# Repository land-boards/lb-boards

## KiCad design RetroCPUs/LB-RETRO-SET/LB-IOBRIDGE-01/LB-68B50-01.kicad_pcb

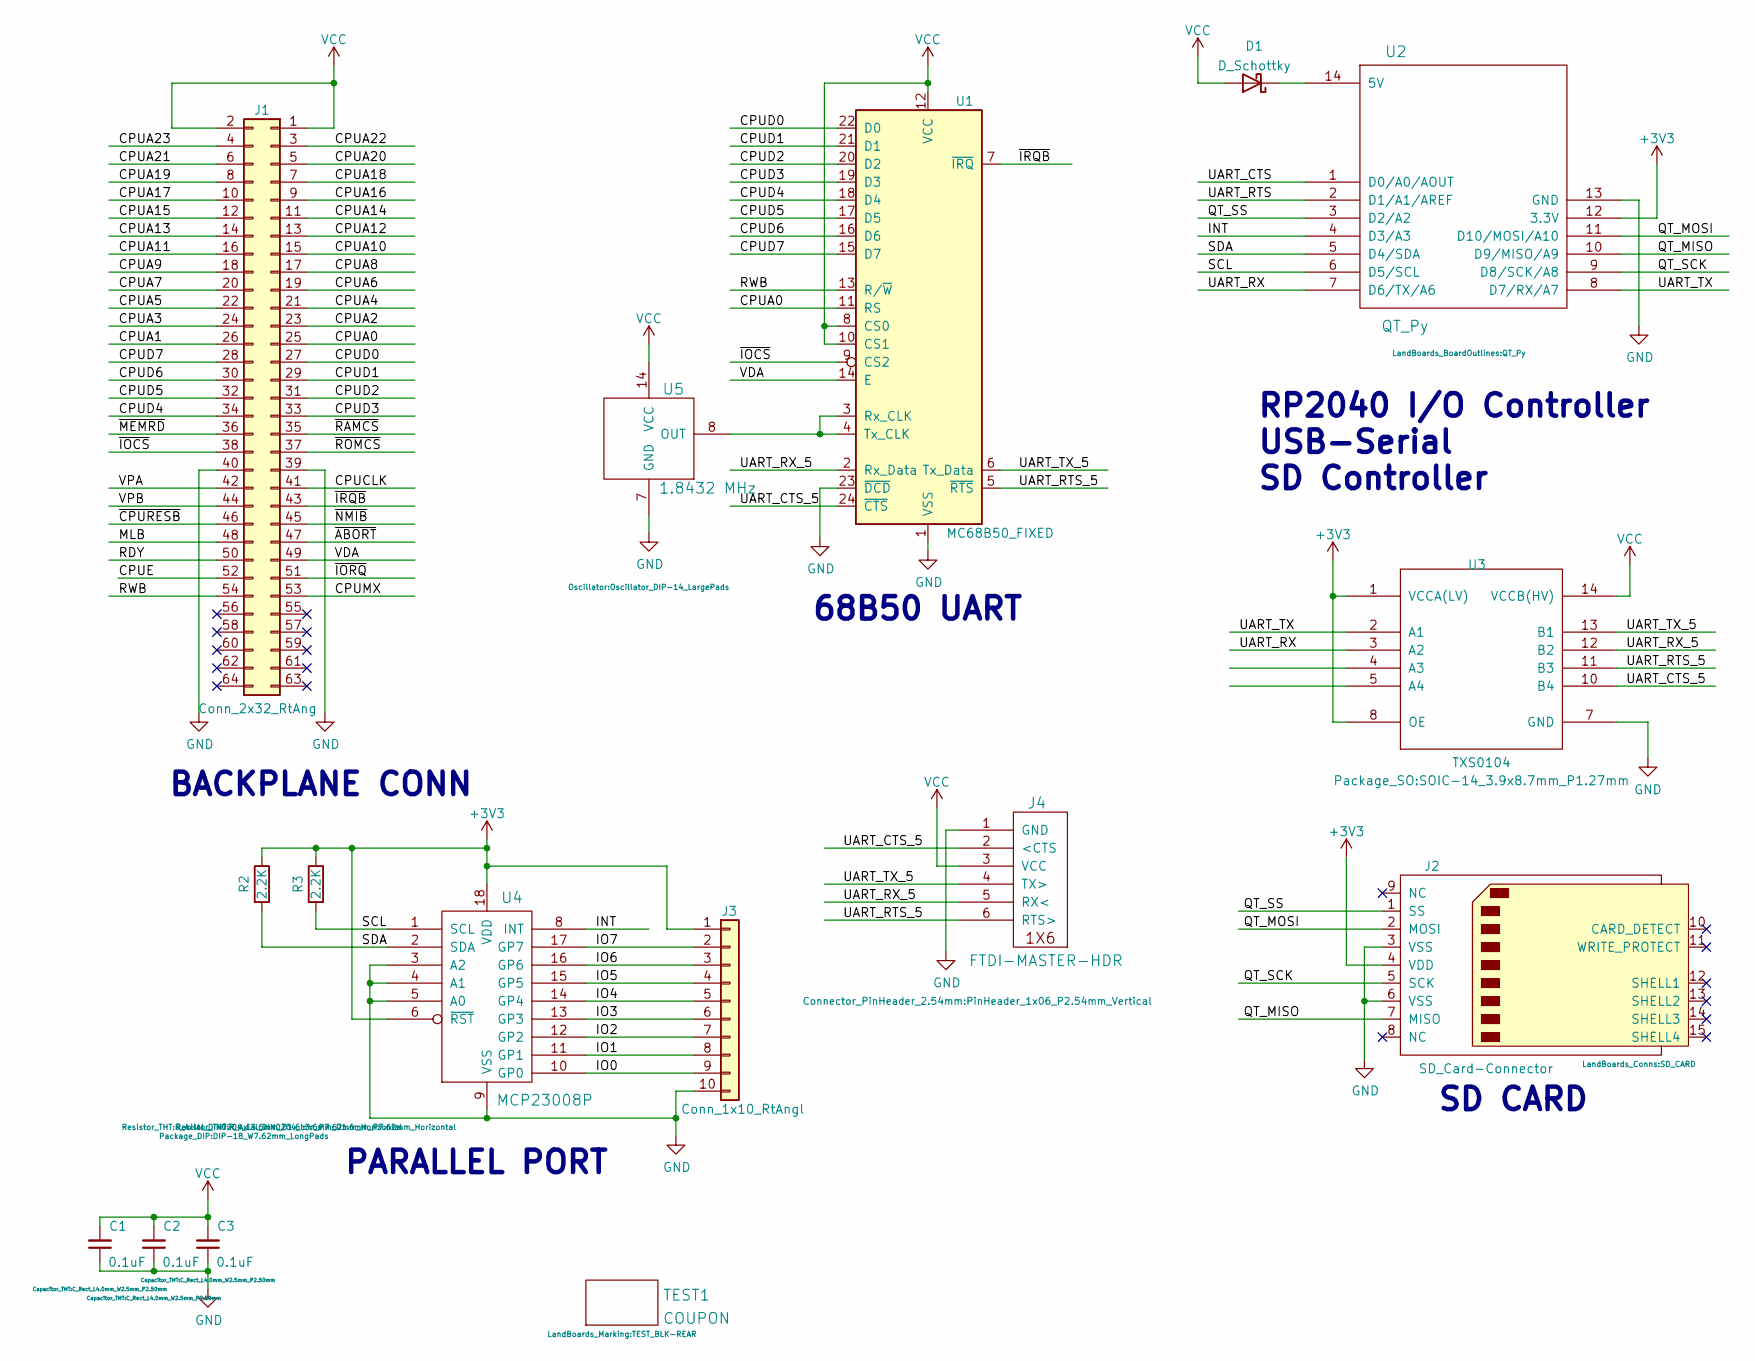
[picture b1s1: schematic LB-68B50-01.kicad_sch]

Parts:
C1, C2, C3: 0.1uF; C_Rect_L4.0mm_W2.5mm_P2.50mm
D1: D_Schottky; D_DO-35_SOD27_P10.16mm_Horizontal
J1: Conn_2x32_RtAng; PinHeader_2x32_P2.54mm_Horizontal-FLIPPED
J2: SD_Card-Connector; SD_CARD
J3: Conn_1x10_RtAngl; PinHeader_1x10_P2.54mm_Horizontal
J4: FTDI-MASTER-HDR; PinHeader_1x06_P2.54mm_Vertical
R2, R3: 2.2K; R_Axial_DIN0204_L3.6mm_D1.6mm_P7.62mm_Horizontal
TEST1: COUPON; TEST_BLK-REAR
U1: MC68B50_FIXED; DIP-24_W15.24mm_LongPads
U2: QT_Py
U3: TXS0104; SOIC-14_3.9x8.7mm_P1.27mm
U4: MCP23008P; DIP-18_W7.62mm_LongPads
U5: 1.8432 MHz; Oscillator_DIP-14_LargePads

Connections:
+3V3: J2.4 (VDD), J3.1, R2.1, R3.1, U2.12 (3.3V), U3.1 (VCCA(LV)), U3.8 (OE), U4.6 (~RST), U4.18 (VDD)
/CPUA0: J1.25, U1.11 (RS)
/CPUA1: J1.26
/CPUA2: J1.23
/CPUA3: J1.24
/CPUA4: J1.21
/CPUA5: J1.22
/CPUA6: J1.19
/CPUA7: J1.20
/CPUA8: J1.17
/CPUA9: J1.18
/CPUA10: J1.15
/CPUA11: J1.16
/CPUA12: J1.13
/CPUA13: J1.14
/CPUA14: J1.11
/CPUA15: J1.12
/CPUA16: J1.9
/CPUA17: J1.10
/CPUA18: J1.7
/CPUA19: J1.8
/CPUA20: J1.5
/CPUA21: J1.6
/CPUA22: J1.3
/CPUA23: J1.4
/CPUCLK: J1.41
/CPUD0: J1.27, U1.22 (D0)
/CPUD1: J1.29, U1.21 (D1)
/CPUD2: J1.31, U1.20 (D2)
/CPUD3: J1.33, U1.19 (D3)
/CPUD4: J1.34, U1.18 (D4)
/CPUD5: J1.32, U1.17 (D5)
/CPUD6: J1.30, U1.16 (D6)
/CPUD7: J1.28, U1.15 (D7)
/CPUE: J1.52
/CPUMX: J1.53
/INT: U2.4 (D3/A3), U4.8 (INT)
/IO0: J3.9, U4.10 (GP0)
/IO1: J3.8, U4.11 (GP1)
/IO2: J3.7, U4.12 (GP2)
/IO3: J3.6, U4.13 (GP3)
/IO4: J3.5, U4.14 (GP4)
/IO5: J3.4, U4.15 (GP5)
/IO6: J3.3, U4.16 (GP6)
/IO7: J3.2, U4.17 (GP7)
/MLB: J1.48
/QT_MISO: J2.7 (MISO), U2.10 (D9/MISO/A9)
/QT_MOSI: J2.2 (MOSI), U2.11 (D10/MOSI/A10)
/QT_SCK: J2.5 (SCK), U2.9 (D8/SCK/A8)
/QT_SS: J2.1 (SS), U2.3 (D2/A2)
/RDY: J1.50
/RWB: J1.54, U1.13 (R/~W)
/SCL: R3.2, U2.6 (D5/SCL), U4.1 (SCL)
/SDA: R2.2, U2.5 (D4/SDA), U4.2 (SDA)
/UART_CTS: U2.1 (D0/A0/AOUT)
/UART_CTS_5: J4.2 (<CTS), U1.24 (~CTS), U3.10 (B4)
/UART_RTS: U2.2 (D1/A1/AREF)
/UART_RTS_5: J4.6 (RTS>), U1.5 (~RTS), U3.11 (B3)
/UART_RX: U2.7 (D6/TX/A6), U3.3 (A2)
/UART_RX_5: J4.5 (RX<), U1.2 (Rx_Data), U3.12 (B2)
/UART_TX: U2.8 (D7/RX/A7), U3.2 (A1)
/UART_TX_5: J4.4 (TX>), U1.6 (Tx_Data), U3.13 (B1)
/VDA: J1.49, U1.14 (E)
/VPA: J1.42
/VPB: J1.44
/~ABORT: J1.47
/~CPURESB: J1.46
/~IOCS: J1.38, U1.9 (CS2)
/~IORQ: J1.51
/~IRQB: J1.43, U1.7 (~IRQ)
/~MEMRD: J1.36
/~NMIB: J1.45
/~RAMCS: J1.35
/~ROMCS: J1.37
GND: C1.1, C2.1, C3.1, J1.39, J1.40, J2.3 (VSS), J2.6 (VSS), J3.10, J4.1 (GND), U1.1 (VSS), U1.23 (~DCD), U2.13 (GND), U3.7 (GND), U4.3 (A2), U4.4 (A1), U4.5 (A0), U4.9 (VSS), U5.7 (GND)
unnamed: D1.1 (K), U2.14 (5V)
unnamed: U1.3 (Rx_CLK), U1.4 (Tx_CLK), U5.8 (OUT)
VCC: C1.2, C2.2, C3.2, D1.2 (A), J1.1, J1.2, J4.3 (VCC), U1.8 (CS0), U1.10 (CS1), U1.12 (VCC), U3.14 (VCCB(HV)), U5.14 (VCC)

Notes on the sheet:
68B50 UART
RP2040 I/O Controller USB-Serial SD Controller
SD CARD
BACKPLANE CONN
PARALLEL PORT

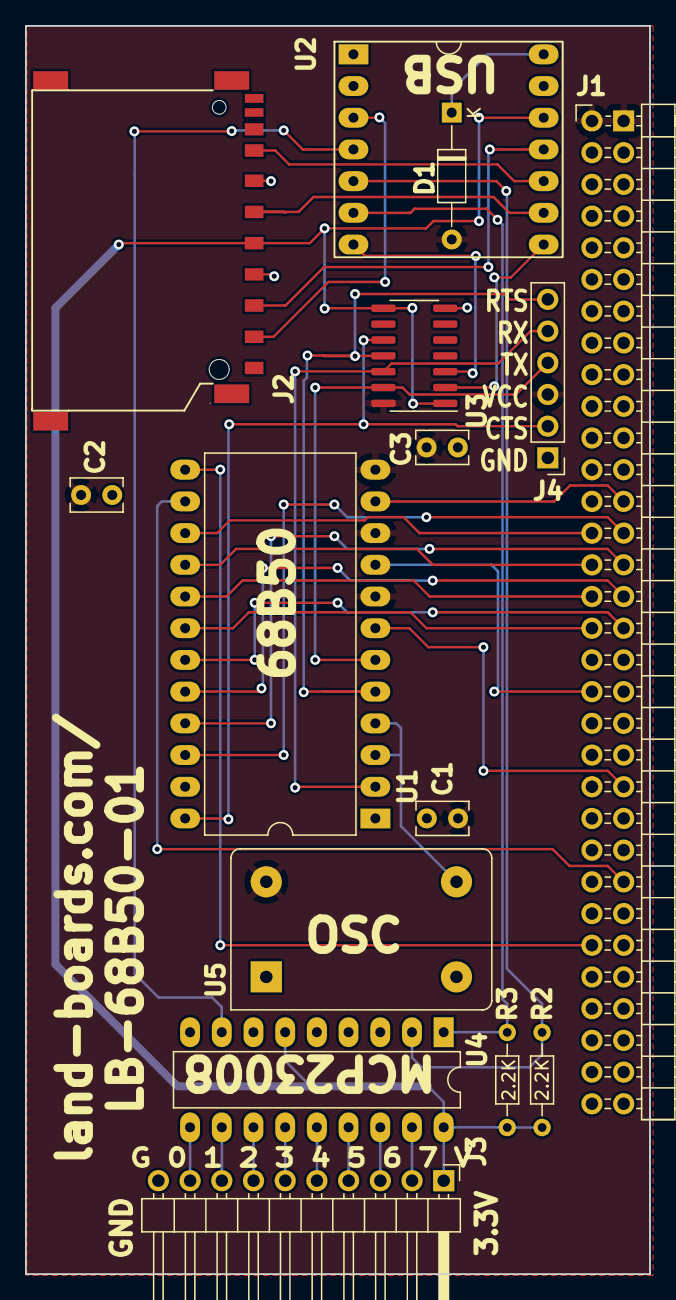
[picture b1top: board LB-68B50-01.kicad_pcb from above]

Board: 2 copper layers, 50.0 x 100.0 mm, 16 parts (0 on the bottom side), 39 nets.

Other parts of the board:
TEST: COUPON; TEST_BLK-REAR

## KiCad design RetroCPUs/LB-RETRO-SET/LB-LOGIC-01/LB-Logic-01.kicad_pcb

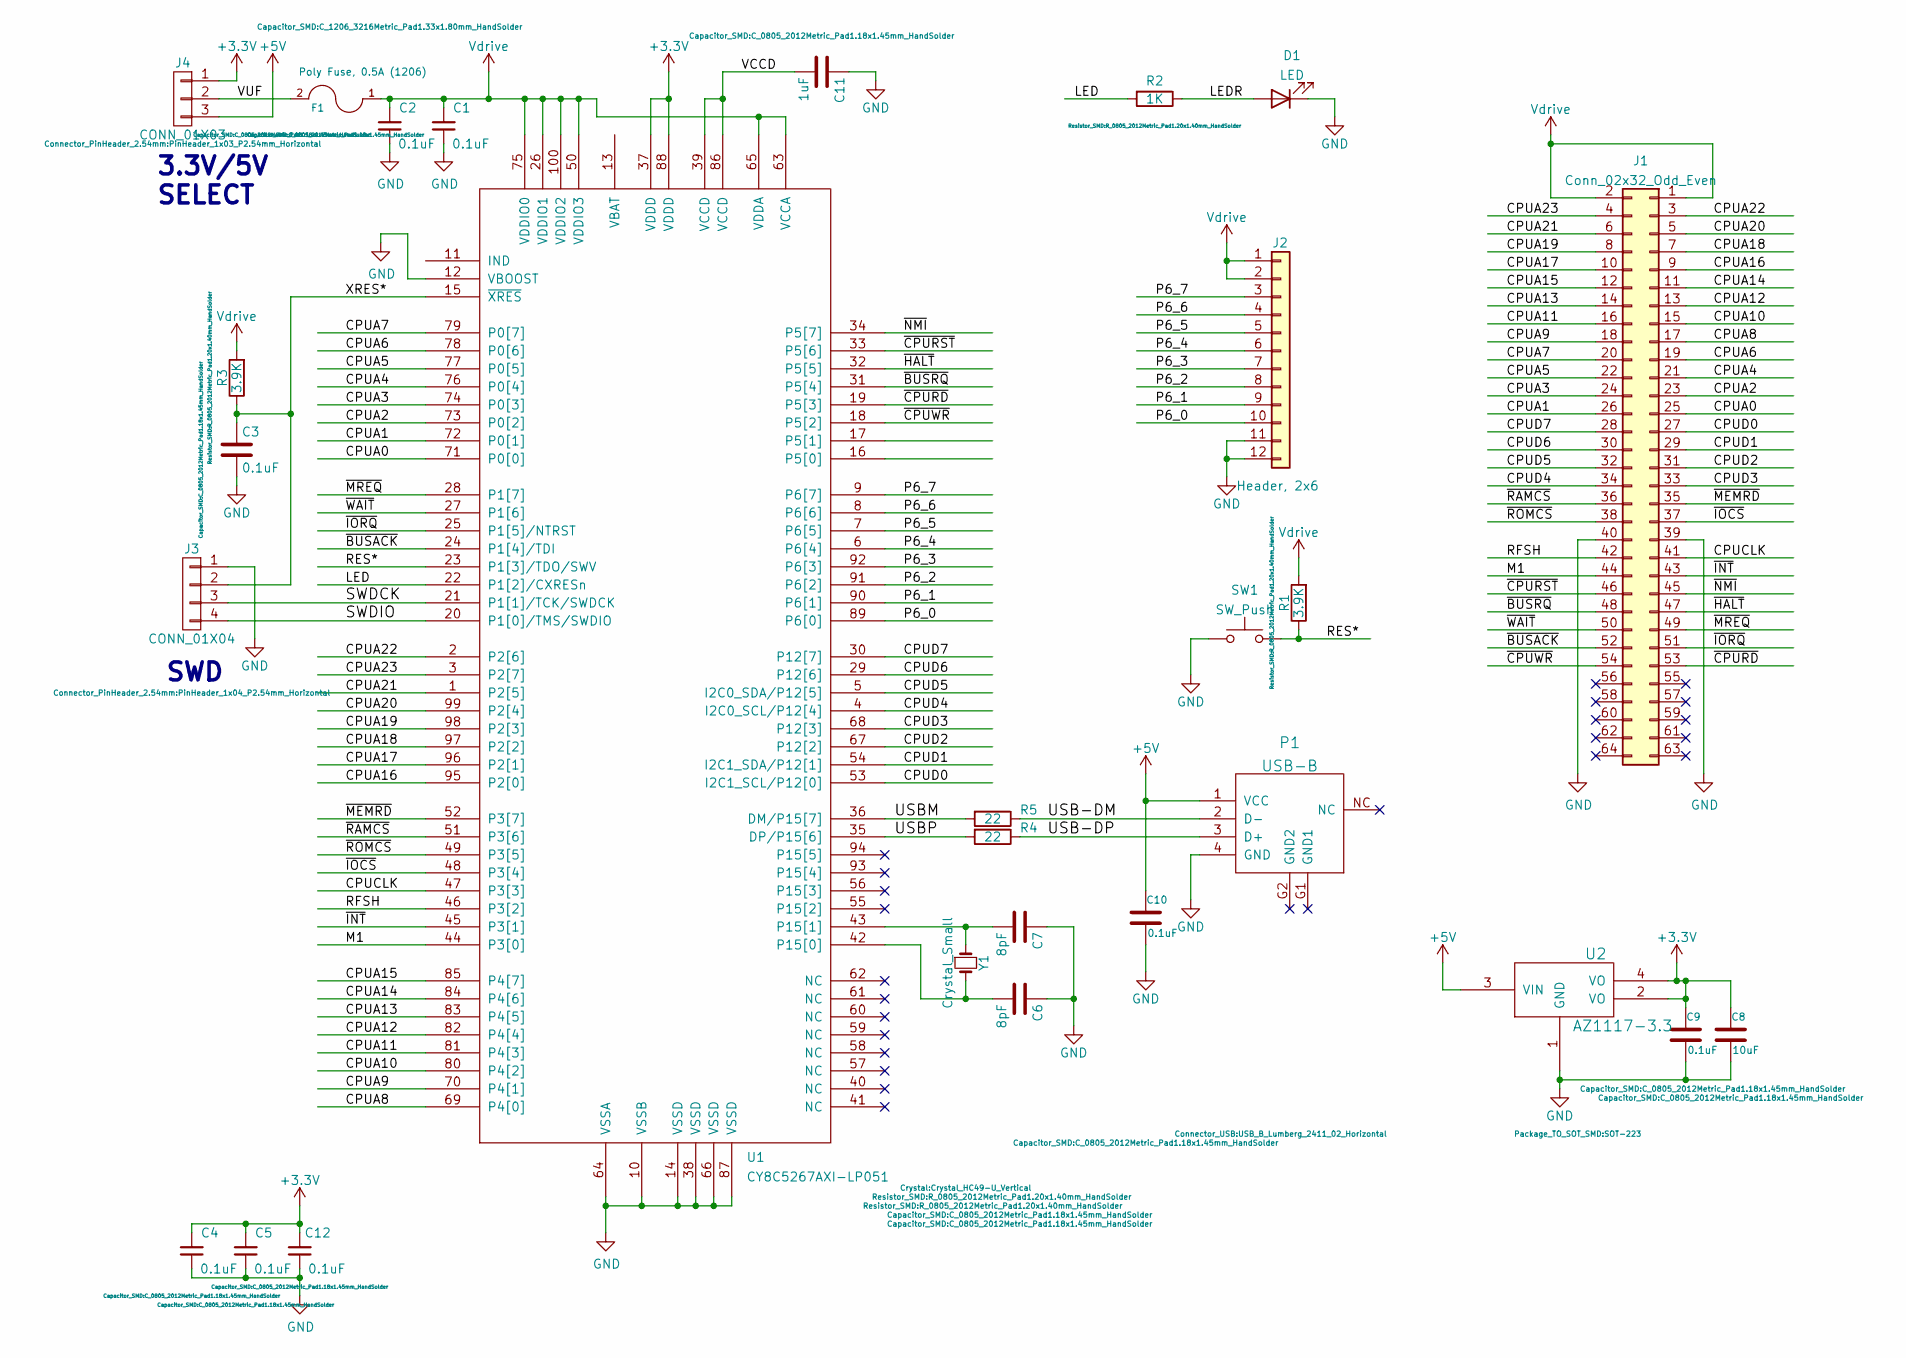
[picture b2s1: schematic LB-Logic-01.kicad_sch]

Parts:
C1, C2, C3, C4, C5, C9, C10, C12: 0.1uF; C_0805_2012Metric_Pad1.18x1.45mm_HandSolder
C6, C7: 8pF; C_0805_2012Metric_Pad1.18x1.45mm_HandSolder
C8: 10uF; C_0805_2012Metric_Pad1.18x1.45mm_HandSolder
C11: 1uF; C_0805_2012Metric_Pad1.18x1.45mm_HandSolder
D1: LED; LED_D3.0mm
F1: Poly Fuse, 0.5A (1206); C_1206_3216Metric_Pad1.33x1.80mm_HandSolder
J1: Conn_02x32_Odd_Even; PinHeader_2x32_P2.54mm_Horizontal-FLIPPED
J2: Header, 2x6; PinHeader_2x06_P2.54mm_Horizontal
J3: CONN_01X04; PinHeader_1x04_P2.54mm_Horizontal
J4: CONN_01X03; PinHeader_1x03_P2.54mm_Horizontal
P1: USB-B; USB_B_Lumberg_2411_02_Horizontal
R1, R3: 3.9K; R_0805_2012Metric_Pad1.20x1.40mm_HandSolder
R2: 1K; R_0805_2012Metric_Pad1.20x1.40mm_HandSolder
R4, R5: 22; R_0805_2012Metric_Pad1.20x1.40mm_HandSolder
SW1: SW_Push; SW_PUSH_6mm_H8.5mm
U1: CY8C5267AXI-LP051; TQFP-100_14x14mm_P0.5mm
U2: AZ1117-3.3; SOT-223
Y1: Crystal_Small; Crystal_HC49-U_Vertical

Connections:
+3V3: C4.2, C5.2, C8.1, C9.1, C12.2, J4.1, U1.37 (VDDD), U1.88 (VDDD), U2.2 (VO), U2.4 (VO)
+5V: C10.1, J4.3, P1.1 (VCC), U2.3 (VIN)
/CPUA0: J1.25, U1.71 (P0[0])
/CPUA1: J1.26, U1.72 (P0[1])
/CPUA2: J1.23, U1.73 (P0[2])
/CPUA3: J1.24, U1.74 (P0[3])
/CPUA4: J1.21, U1.76 (P0[4])
/CPUA5: J1.22, U1.77 (P0[5])
/CPUA6: J1.19, U1.78 (P0[6])
/CPUA7: J1.20, U1.79 (P0[7])
/CPUA8: J1.17, U1.69 (P4[0])
/CPUA9: J1.18, U1.70 (P4[1])
/CPUA10: J1.15, U1.80 (P4[2])
/CPUA11: J1.16, U1.81 (P4[3])
/CPUA12: J1.13, U1.82 (P4[4])
/CPUA13: J1.14, U1.83 (P4[5])
/CPUA14: J1.11, U1.84 (P4[6])
/CPUA15: J1.12, U1.85 (P4[7])
/CPUA16: J1.9, U1.95 (P2[0])
/CPUA17: J1.10, U1.96 (P2[1])
/CPUA18: J1.7, U1.97 (P2[2])
/CPUA19: J1.8, U1.98 (P2[3])
/CPUA20: J1.5, U1.99 (P2[4])
/CPUA21: J1.6, U1.1 (P2[5])
/CPUA22: J1.3, U1.2 (P2[6])
/CPUA23: J1.4, U1.3 (P2[7])
/CPUCLK: J1.41, U1.47 (P3[3])
/CPUD0: J1.27, U1.53 (I2C1_SCL/P12[0])
/CPUD1: J1.29, U1.54 (I2C1_SDA/P12[1])
/CPUD2: J1.31, U1.67 (P12[2])
/CPUD3: J1.33, U1.68 (P12[3])
/CPUD4: J1.34, U1.4 (I2C0_SCL/P12[4])
/CPUD5: J1.32, U1.5 (I2C0_SDA/P12[5])
/CPUD6: J1.30, U1.29 (P12[6])
/CPUD7: J1.28, U1.30 (P12[7])
/LED: R2.2, U1.22 (P1[2]/CXRESn)
/LEDR: D1.2 (A), R2.1
/M1: J1.44, U1.44 (P3[0])
/P6_0: J2.10, U1.89 (P6[0])
/P6_1: J2.9, U1.90 (P6[1])
/P6_2: J2.8, U1.91 (P6[2])
/P6_3: J2.7, U1.92 (P6[3])
/P6_4: J2.6, U1.6 (P6[4])
/P6_5: J2.5, U1.7 (P6[5])
/P6_6: J2.4, U1.8 (P6[6])
/P6_7: J2.3, U1.9 (P6[7])
/RES*: R1.1, SW1.2, U1.23 (P1[3]/TDO/SWV)
/RFSH: J1.42, U1.46 (P3[2])
/SWDCK: J3.3, U1.21 (P1[1]/TCK/SWDCK)
/SWDIO: J3.4, U1.20 (P1[0]/TMS/SWDIO)
/USB-DM: P1.2 (D-), R5.1
/USB-DP: P1.3 (D+), R4.1
/USBM: R5.2, U1.36 (DM/P15[7])
/USBP: R4.2, U1.35 (DP/P15[6])
/VCCD: C11.2, U1.39 (VCCD), U1.86 (VCCD)
/VUF: F1.2, J4.2
/XRES*: C3.1, J3.2, R3.1, U1.15 (~XRES)
/~BUSACK: J1.52, U1.24 (P1[4]/TDI)
/~BUSRQ: J1.48, U1.31 (P5[4])
/~CPURD: J1.53, U1.19 (P5[3])
/~CPURST: J1.46, U1.33 (P5[6])
/~CPUWR: J1.54, U1.18 (P5[2])
/~HALT: J1.47, U1.32 (P5[5])
/~INT: J1.43, U1.45 (P3[1])
/~IOCS: J1.37, U1.48 (P3[4])
/~IORQ: J1.51, U1.25 (P1[5]/NTRST)
/~MEMRD: J1.35, U1.52 (P3[7])
/~MREQ: J1.49, U1.28 (P1[7])
/~NMI: J1.45, U1.34 (P5[7])
/~RAMCS: J1.36, U1.51 (P3[6])
/~ROMCS: J1.38, U1.49 (P3[5])
/~WAIT: J1.50, U1.27 (P1[6])
GND: C1.1, C2.1, C3.2, C4.1, C5.1, C6.1, C7.1, C8.2, C9.2, C10.2, C11.1, C12.1, D1.1 (K), J1.39, J1.40, J2.11, J2.12, J3.1, P1.4 (GND), SW1.1, U1.10 (VSSB), U1.12 (VBOOST), U1.14 (VSSD), U1.38 (VSSD), U1.64 (VSSA), U1.66 (VSSD), U1.87 (VSSD), U2.1 (GND)
unnamed: C6.2, U1.42 (P15[0]), Y1.2
unnamed: C7.2, U1.43 (P15[1]), Y1.1
Vdrive: C1.2, C2.2, F1.1, J1.1, J1.2, J2.1, J2.2, R1.2, R3.2, U1.26 (VDDIO1), U1.50 (VDDIO3), U1.63 (VCCA), U1.65 (VDDA), U1.75 (VDDIO0), U1.100 (VDDIO2)

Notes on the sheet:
SWD
3.3V/5V SELECT

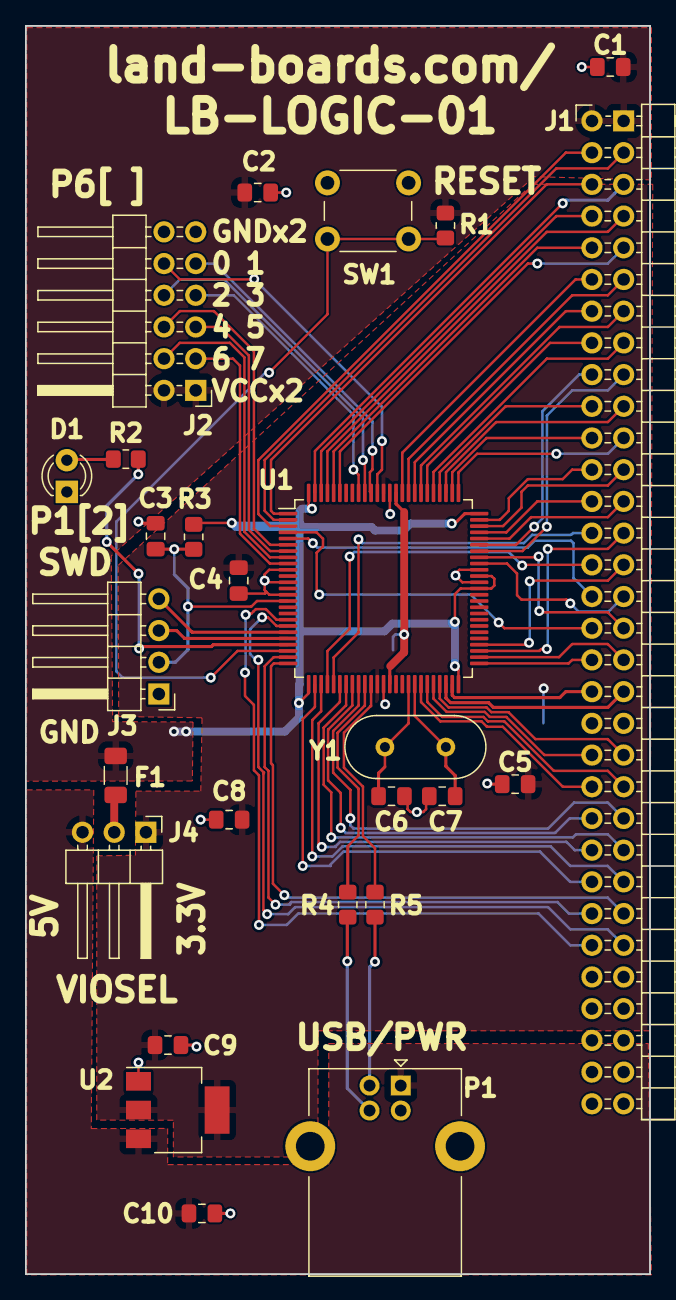
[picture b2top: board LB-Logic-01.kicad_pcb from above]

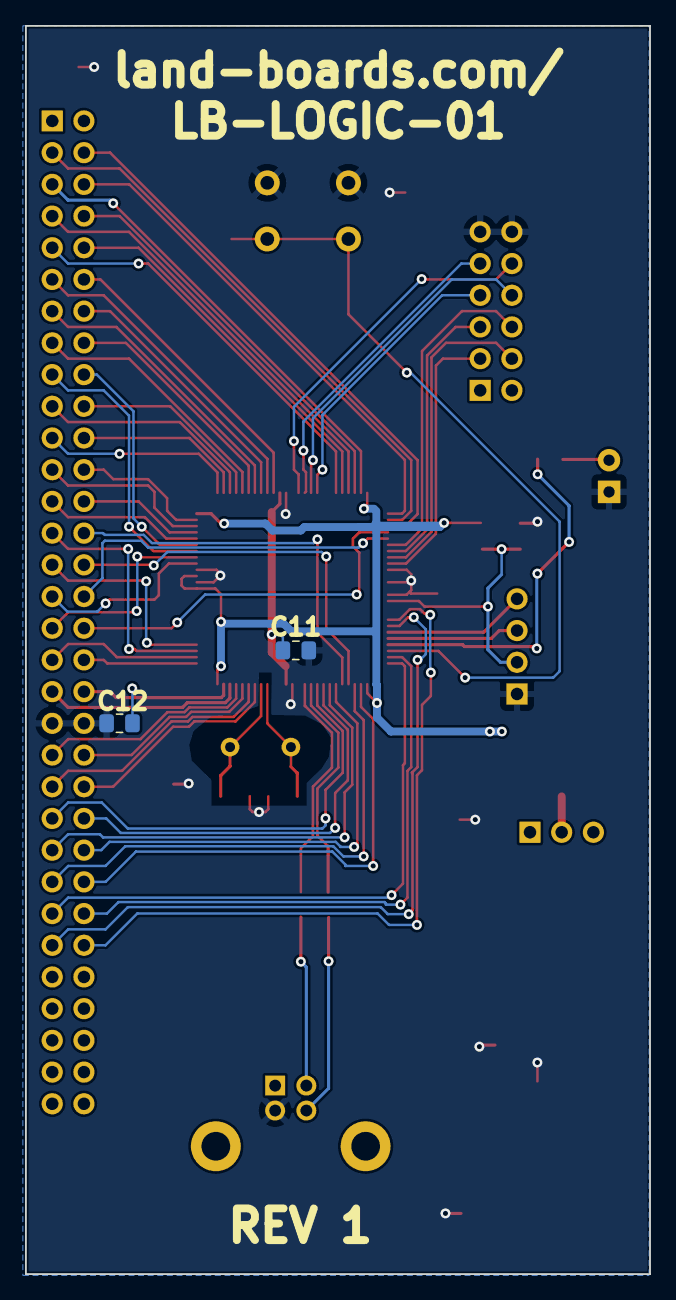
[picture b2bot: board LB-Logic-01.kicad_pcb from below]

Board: 2 copper layers, 50.0 x 100.0 mm, 28 parts (2 on the bottom side), 76 nets.

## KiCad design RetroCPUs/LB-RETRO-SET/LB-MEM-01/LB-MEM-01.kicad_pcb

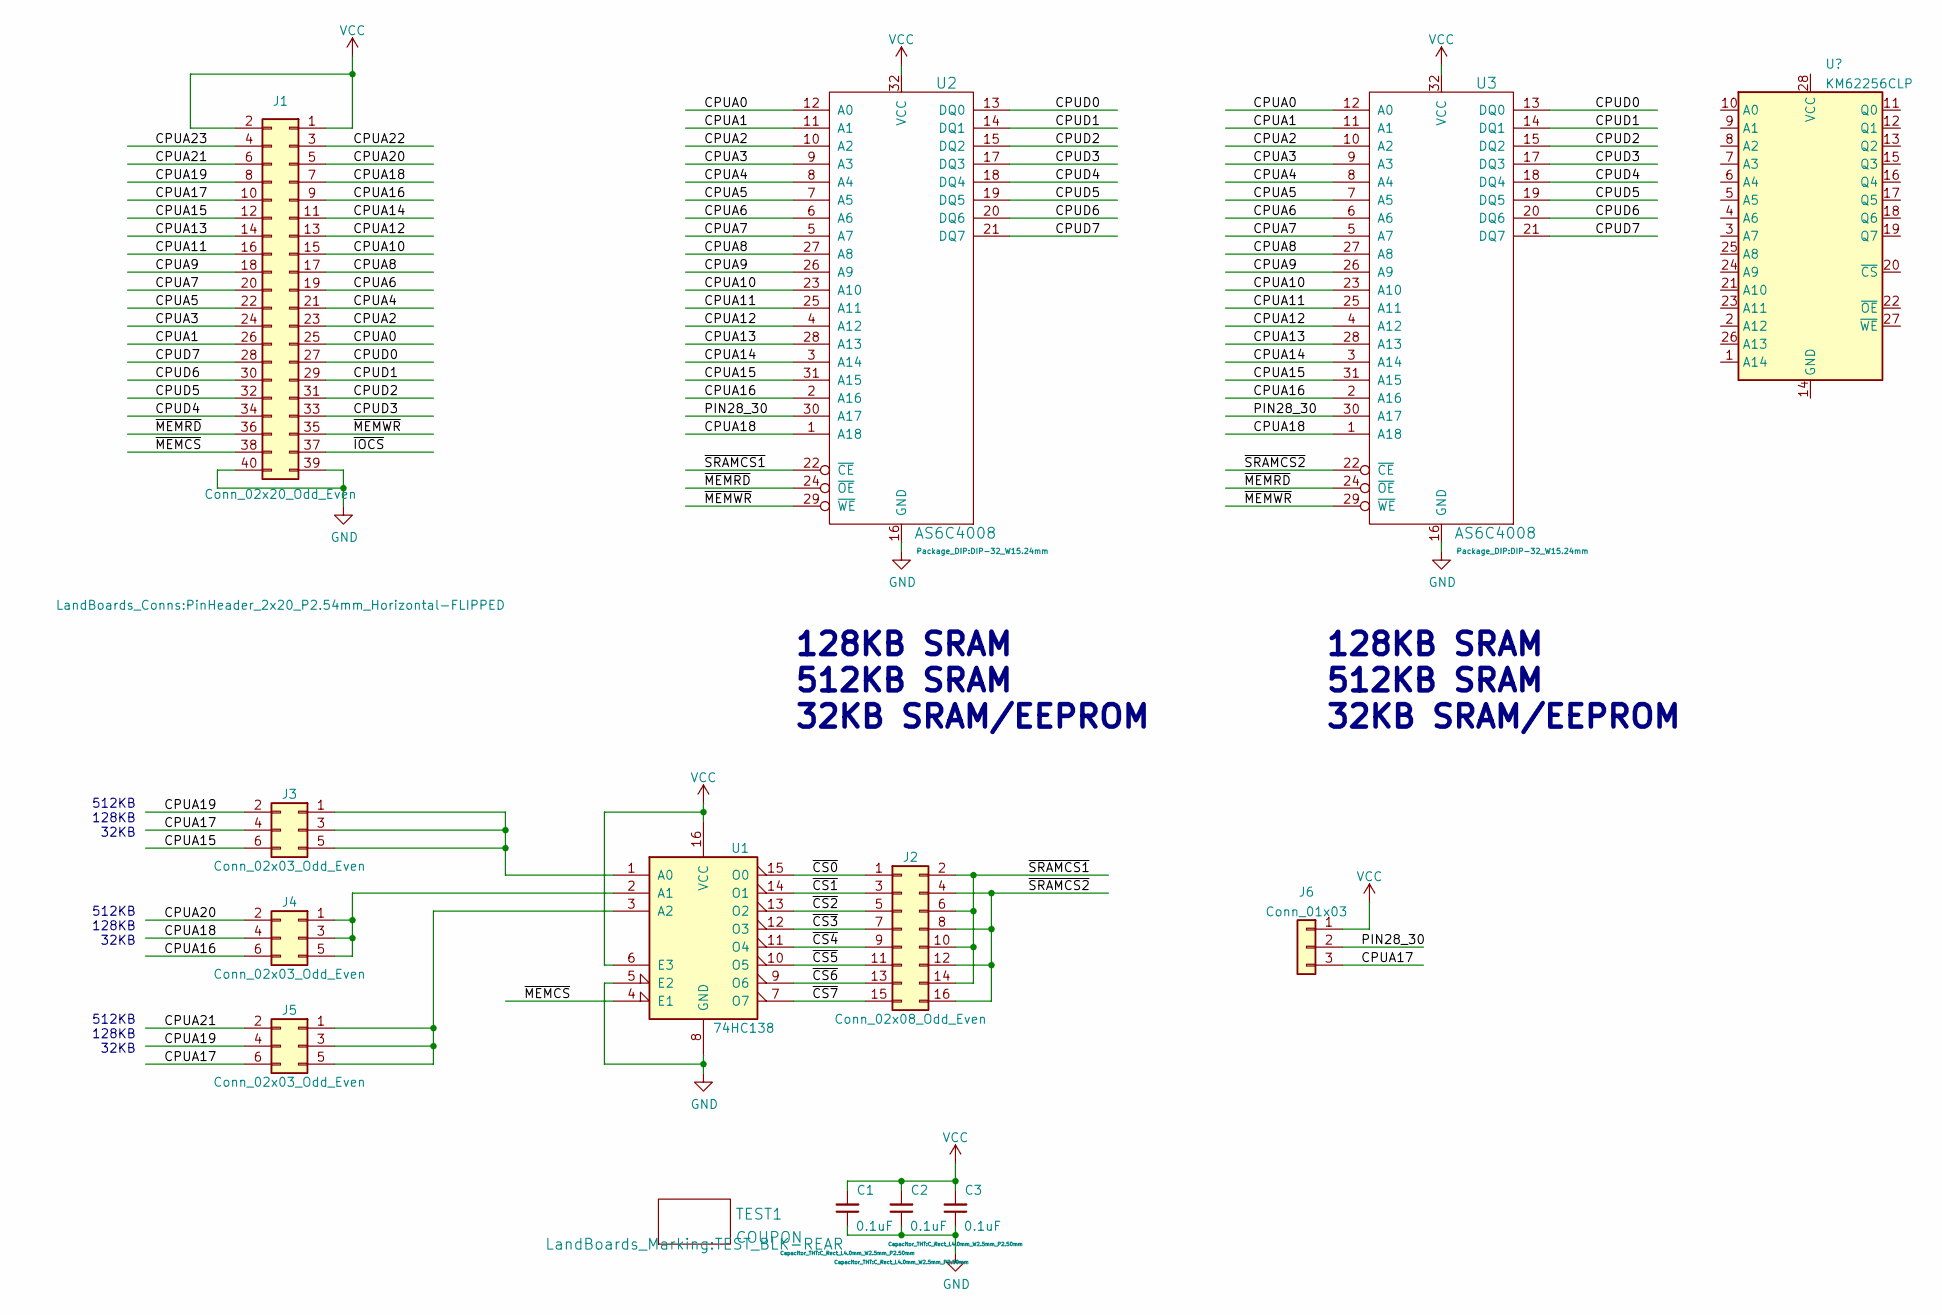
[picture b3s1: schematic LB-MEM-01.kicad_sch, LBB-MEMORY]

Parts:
C1, C2, C3: 0.1uF; C_Rect_L4.0mm_W2.5mm_P2.50mm
J1: Conn_02x20_Odd_Even; PinHeader_2x20_P2.54mm_Horizontal-FLIPPED
J2: Conn_02x08_Odd_Even; PinHeader_2x08_P2.54mm_Vertical
J3, J4, J5: Conn_02x03_Odd_Even; PinHeader_2x03_P2.54mm_Vertical
J6: Conn_01x03; PinHeader_1x03_P2.54mm_Vertical
TEST1: COUPON; TEST_BLK-REAR
U1: 74HC138; DIP-16_W7.62mm
U2, U3: AS6C4008; DIP-32_W15.24mm

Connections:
/CPUA0: J1.25, U2.12 (A0), U3.12 (A0)
/CPUA1: J1.26, U2.11 (A1), U3.11 (A1)
/CPUA2: J1.23, U2.10 (A2), U3.10 (A2)
/CPUA3: J1.24, U2.9 (A3), U3.9 (A3)
/CPUA4: J1.21, U2.8 (A4), U3.8 (A4)
/CPUA5: J1.22, U2.7 (A5), U3.7 (A5)
/CPUA6: J1.19, U2.6 (A6), U3.6 (A6)
/CPUA7: J1.20, U2.5 (A7), U3.5 (A7)
/CPUA8: J1.17, U2.27 (A8), U3.27 (A8)
/CPUA9: J1.18, U2.26 (A9), U3.26 (A9)
/CPUA10: J1.15, U2.23 (A10), U3.23 (A10)
/CPUA11: J1.16, U2.25 (A11), U3.25 (A11)
/CPUA12: J1.13, U2.4 (A12), U3.4 (A12)
/CPUA13: J1.14, U2.28 (A13), U3.28 (A13)
/CPUA14: J1.11, U2.3 (A14), U3.3 (A14)
/CPUA15: J1.12, J3.6, U2.31 (A15), U3.31 (A15)
/CPUA16: J1.9, J4.6, U2.2 (A16), U3.2 (A16)
/CPUA17: J1.10, J3.4, J5.6, J6.3
/CPUA18: J1.7, J4.4, U2.1 (A18), U3.1 (A18)
/CPUA19: J1.8, J3.2, J5.4
/CPUA20: J1.5, J4.2
/CPUA21: J1.6, J5.2
/CPUA22: J1.3
/CPUA23: J1.4
/CPUD0: J1.27, U2.13 (DQ0), U3.13 (DQ0)
/CPUD1: J1.29, U2.14 (DQ1), U3.14 (DQ1)
/CPUD2: J1.31, U2.15 (DQ2), U3.15 (DQ2)
/CPUD3: J1.33, U2.17 (DQ3), U3.17 (DQ3)
/CPUD4: J1.34, U2.18 (DQ4), U3.18 (DQ4)
/CPUD5: J1.32, U2.19 (DQ5), U3.19 (DQ5)
/CPUD6: J1.30, U2.20 (DQ6), U3.20 (DQ6)
/CPUD7: J1.28, U2.21 (DQ7), U3.21 (DQ7)
/PIN28_30: J6.2, U2.30 (A17), U3.30 (A17)
/~CS0: J2.1, U1.15 (O0)
/~CS1: J2.3, U1.14 (O1)
/~CS2: J2.5, U1.13 (O2)
/~CS3: J2.7, U1.12 (O3)
/~CS4: J2.9, U1.11 (O4)
/~CS5: J2.11, U1.10 (O5)
/~CS6: J2.13, U1.9 (O6)
/~CS7: J2.15, U1.7 (O7)
/~IOCS: J1.37
/~MEMCS: J1.38, U1.4 (E1)
/~MEMRD: J1.36, U2.24 (~OE), U3.24 (~OE)
/~MEMWR: J1.35, U2.29 (~WE), U3.29 (~WE)
/~SRAMCS1: J2.2, J2.6, J2.10, J2.14, U2.22 (~CE)
/~SRAMCS2: J2.4, J2.8, J2.12, J2.16, U3.22 (~CE)
GND: C1.1, C2.1, C3.1, J1.39, J1.40, U1.5 (E2), U1.8 (GND), U2.16 (GND), U3.16 (GND)
unnamed: J3.1, J3.3, J3.5, U1.1 (A0)
unnamed: J4.1, J4.3, J4.5, U1.2 (A1)
unnamed: J5.1, J5.3, J5.5, U1.3 (A2)
VCC: C1.2, C2.2, C3.2, J1.1, J1.2, J6.1, U1.6 (E3), U1.16 (VCC), U2.32 (VCC), U3.32 (VCC)

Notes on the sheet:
512KB 128KB 32KB
128KB SRAM 512KB SRAM 32KB SRAM/EEPROM

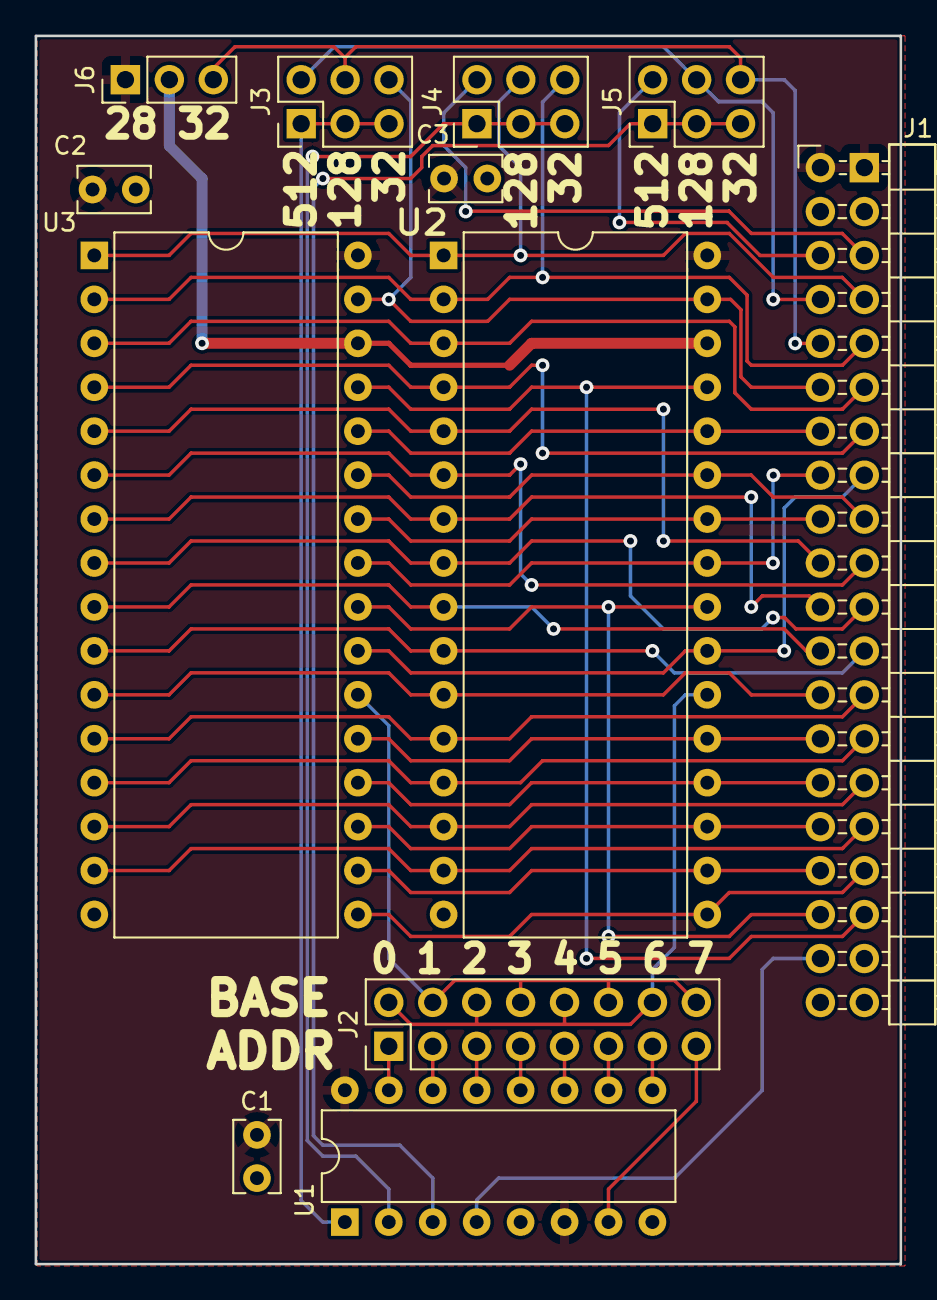
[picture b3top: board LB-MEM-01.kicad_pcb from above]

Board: 2 copper layers, 50.0 x 71.0 mm, 13 parts (0 on the bottom side), 49 nets.

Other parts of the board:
TEST: COUPON; TEST_BLK-REAR

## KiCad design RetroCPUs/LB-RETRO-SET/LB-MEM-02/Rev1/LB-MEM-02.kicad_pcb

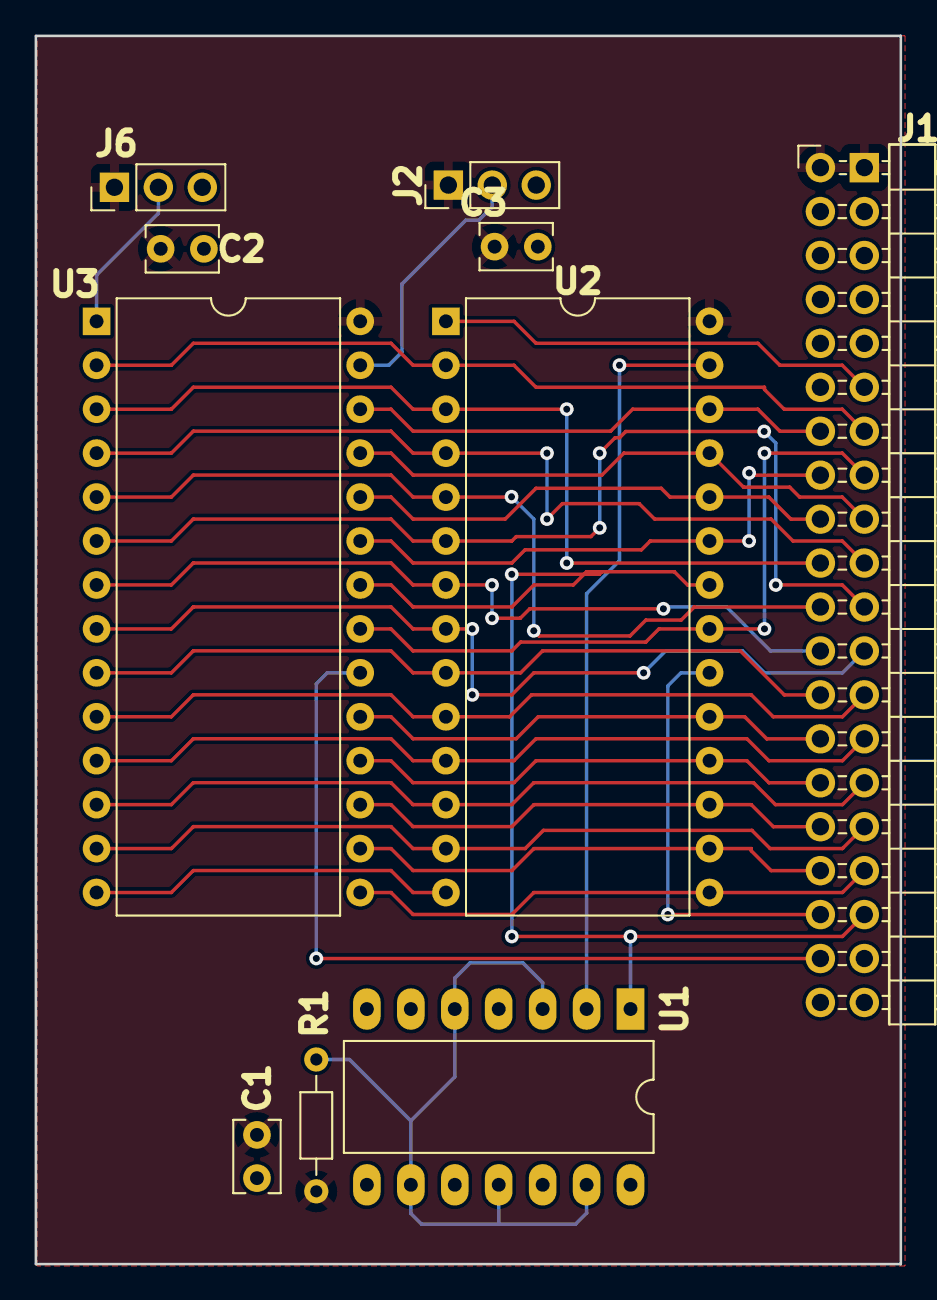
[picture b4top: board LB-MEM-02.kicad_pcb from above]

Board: 2 copper layers, 50.0 x 71.0 mm, 11 parts (0 on the bottom side), 32 nets.

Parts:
C1, C2, C3: 0.1uF; C_Rect_L4.0mm_W2.5mm_P2.50mm
J1: Conn_02x20_Odd_Even; PinHeader_2x20_P2.54mm_Horizontal-FLIPPED
J2, J6: Conn_01x03; PinHeader_1x03_P2.54mm_Vertical
R1: 2.7K; R_Axial_DIN0204_L3.6mm_D1.6mm_P7.62mm_Horizontal
TEST: COUPON; TEST_BLK-REAR
U1: 74HC04; DIP-14_W10.16mm_LongPads
U2: HM62256BLP; DIP-28_W15.24mm
U3: 27C128; DIP-28_W15.24mm

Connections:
/CPUA0: J1.25, U2.10 (A0), U3.10 (A0)
/CPUA1: J1.26, U2.9 (A1), U3.9 (A1)
/CPUA2: J1.23, U2.8 (A2), U3.8 (A2)
/CPUA3: J1.24, U2.7 (A3), U3.7 (A3)
/CPUA4: J1.21, U2.6 (A4), U3.6 (A4)
/CPUA5: J1.22, U2.5 (A5), U3.5 (A5)
/CPUA6: J1.19, U2.4 (A6), U3.4 (A6)
/CPUA7: J1.20, U2.3 (A7), U3.3 (A7)
/CPUA8: J1.17, U2.25 (A8), U3.25 (A8)
/CPUA9: J1.18, U2.24 (A9), U3.24 (A9)
/CPUA10: J1.15, U2.21 (A10), U3.21 (A10)
/CPUA11: J1.16, U2.23 (A11), U3.23 (A11)
/CPUA12: J1.13, U2.2 (A12), U3.2 (A12)
/CPUA13: J1.14, U2.26 (A13), U3.26 (A13)
/CPUA14: J1.11, U2.1 (A14)
/CPUD0: J1.27, U2.11 (Q0), U3.11 (D0)
/CPUD1: J1.29, U2.12 (Q1), U3.12 (D1)
/CPUD2: J1.31, U2.13 (Q2), U3.13 (D2)
/CPUD3: J1.33, U2.15 (Q3), U3.15 (D3)
/CPUD4: J1.34, U2.16 (Q4), U3.16 (D4)
/CPUD5: J1.32, U2.17 (Q5), U3.17 (D5)
/CPUD6: J1.30, U2.18 (Q6), U3.18 (D6)
/CPUD7: J1.28, U2.19 (Q7), U3.19 (D7)
/EE_PIN1: J6.2, U3.1 (VPP)
/EE_PIN27: J2.2, U3.27 (~PGM)
/~MEMRD: J1.35, U1.1, U2.22 (~OE), U3.22 (~OE)
/~MEMWR: U1.2, U2.27 (~WE)
/~RAMCS: J1.36, U2.20 (~CS)
/~ROMCS: J1.38, U3.20 (~CE)
GND: C1.1, C2.1, C3.1, J1.39, J1.40, J2.3, J6.3, U2.14 (GND), U3.14 (GND)
unnamed: R1.2, U1.3, U1.5, U1.9, U1.11, U1.13
VCC: C1.2, C2.2, C3.2, J1.1, J1.2, J2.1, J6.1, R1.1, U2.28 (VCC), U3.28 (VCC)

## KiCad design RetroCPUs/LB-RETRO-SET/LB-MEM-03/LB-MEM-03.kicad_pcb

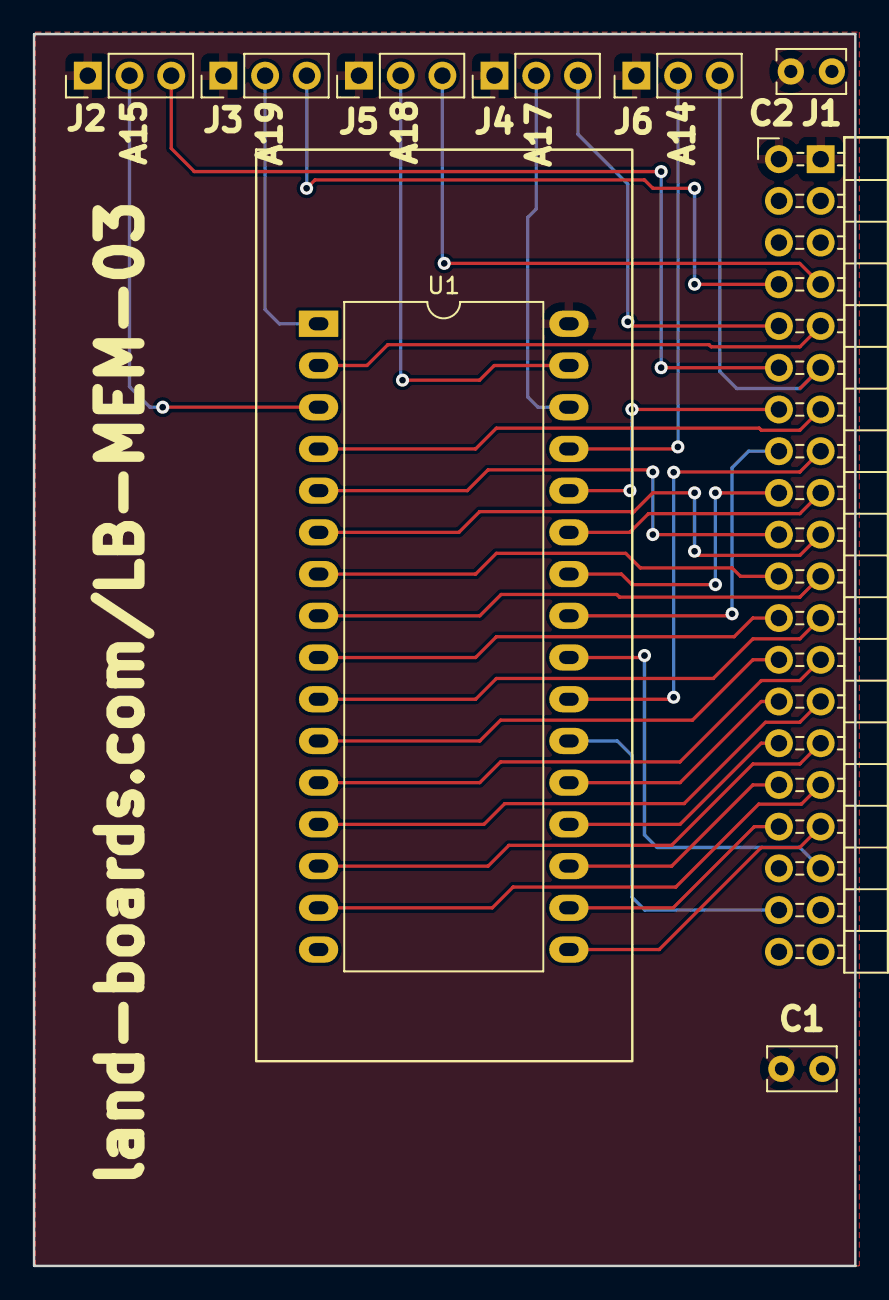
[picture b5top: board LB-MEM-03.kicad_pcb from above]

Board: 2 copper layers, 50.0 x 75.0 mm, 10 parts (0 on the bottom side), 37 nets.

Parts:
C1, C2: 0.1uF; C_Rect_L4.0mm_W2.5mm_P2.50mm
J1: Conn_02x20_Odd_Even; PinHeader_2x20_P2.54mm_Horizontal-FLIPPED
J2, J3, J4, J5, J6: Conn_01x03; PinHeader_1x03_P2.54mm_Vertical
TEST: COUPON; TEST_BLK-REAR
U1: 27C080; DIP-32_W15.24mm_TEXTOOL

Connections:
/CPUA0: J1.25, U1.12 (A0)
/CPUA1: J1.26, U1.11 (A1)
/CPUA2: J1.23, U1.10 (A2)
/CPUA3: J1.24, U1.9 (A3)
/CPUA4: J1.21, U1.8 (A4)
/CPUA5: J1.22, U1.7 (A5)
/CPUA6: J1.19, U1.6 (A6)
/CPUA7: J1.20, U1.5 (A7)
/CPUA8: J1.17, U1.27 (A8)
/CPUA9: J1.18, U1.26 (A9)
/CPUA10: J1.15, U1.23 (A10)
/CPUA11: J1.16, U1.25 (A11)
/CPUA12: J1.13, U1.4 (A12)
/CPUA13: J1.14, U1.28 (A13)
/CPUA14: J1.11, J6.3
/CPUA15: J1.12, J2.3
/CPUA16: J1.9, U1.2 (A16)
/CPUA17: J1.10, J4.3
/CPUA18: J1.7, J5.3
/CPUA19: J1.8, J3.3
/CPUD0: J1.27, U1.13 (D0)
/CPUD1: J1.29, U1.14 (D1)
/CPUD2: J1.31, U1.15 (D2)
/CPUD3: J1.33, U1.17 (D3)
/CPUD4: J1.34, U1.18 (D4)
/CPUD5: J1.32, U1.19 (D5)
/CPUD6: J1.30, U1.20 (D6)
/CPUD7: J1.28, U1.21 (D7)
/EE_PIN1: J3.2, U1.1 (A19)
/EE_PIN3: J2.2, U1.3 (A15)
/EE_PIN29: J6.2, U1.29 (A14)
/EE_PIN30: J4.2, U1.30 (A17)
/EE_PIN31: J5.2, U1.31 (A18)
/~MEMRD: J1.35, U1.24 (~OE)
/~ROMCS: J1.38, U1.22 (~CE)
GND: C1.1, C2.1, J1.39, J1.40, U1.16 (GND)
VCC: C1.2, C2.2, J1.1, J1.2, J2.1, J3.1, J4.1, J5.1, J6.1, U1.32 (VCC)
